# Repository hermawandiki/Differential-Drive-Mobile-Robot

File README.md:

# Differential-Drive-Mobile-Robot

This DDMR is equipped with a GUI that is able to display sensor data from the robot, control the movement of the robot, and set PID parameters for the speed of each motor.

This project was developed in the mechatronics system programming course at Mechatronics Engineering - EEPIS

Course lecturer : Adytia Darmawan, S.ST., M.T.

Mechatronics Engineering Study Program

Electronic Engineering Polytechnic Institute of Surabaya (EEPIS)

#

DDMR ini dilengkapi dengan GUI yang mampu menampilkan data sensor dari robot, mengendalikan pergerakan robot, dan mengatur parameter PID untuk kecepatan setiap motor.

Proyek ini dikembangkan dalam mata kuliah pemrograman sistem mekatronika di Teknik Mekatronika - PENS

Dosen Mata Kuliah : Adytia Darmawan, S.ST., M.T.

Program Studi Teknik Mekatronika

Politeknik Elektronika Negeri Surabaya (PENS)

#

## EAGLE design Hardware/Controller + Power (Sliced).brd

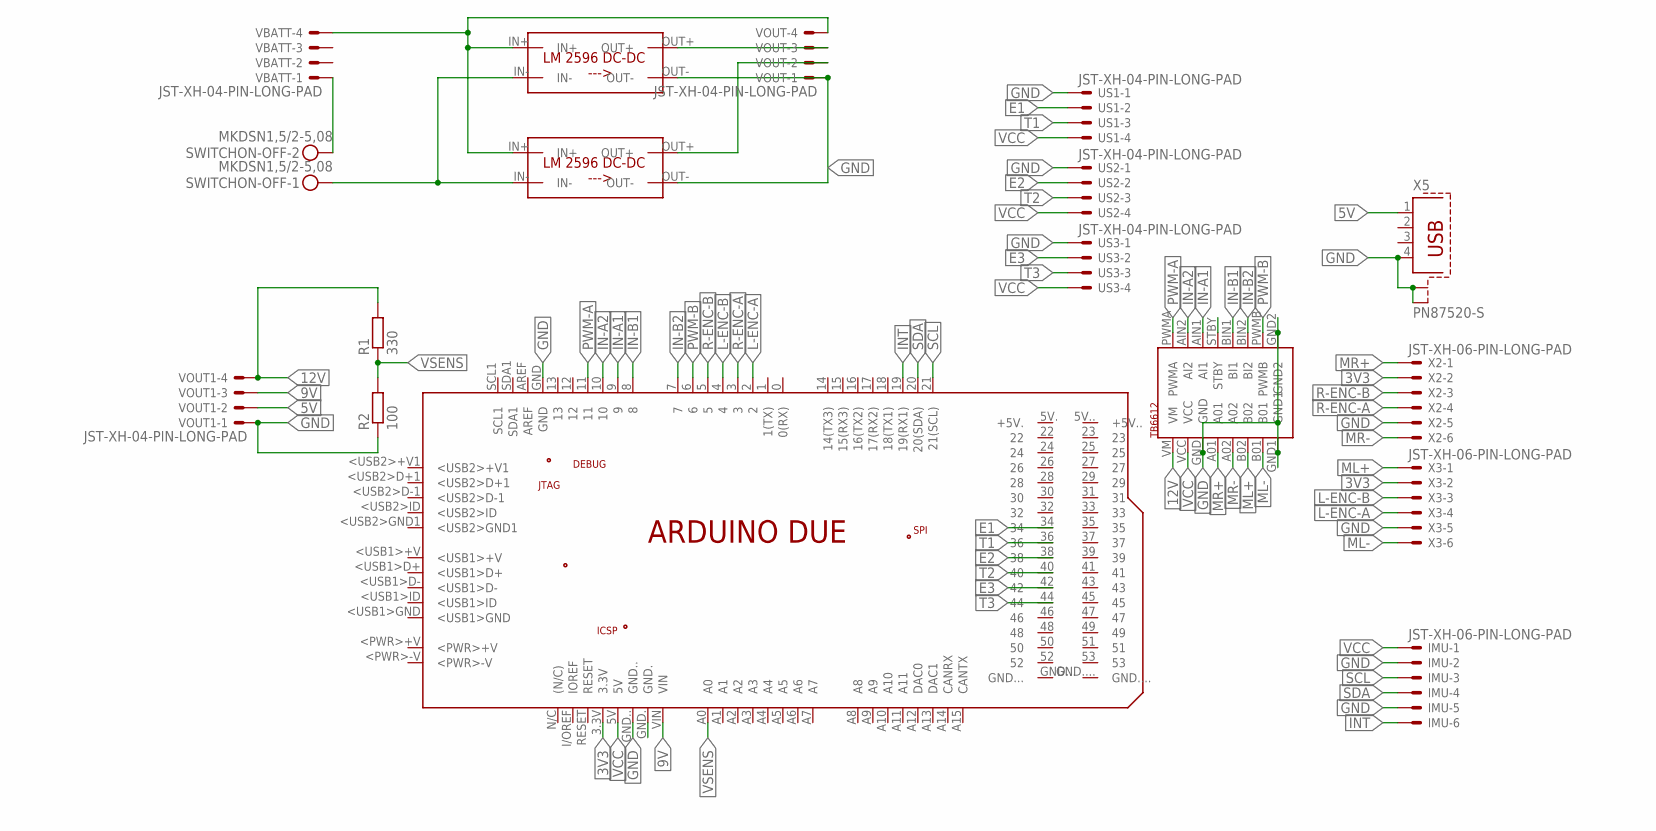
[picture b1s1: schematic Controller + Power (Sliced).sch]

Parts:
IMU: JST-XH-06-PIN-LONG-PAD; JST-XH-06-PACKAGE-LONG-PAD
PCB1: ARDUINO_DUE
R1: 330; R1206
R2: 100; R1206
SWITCHON-OFF: MKDSN1,5/2-5,08
U$1, U$2: LM2596_MODBUCK; LM2596_MOD
U$3: TB6612
US1, US2, US3: JST-XH-04-PIN-LONG-PAD; JST-XH-04-PACKAGE-LONG-PAD
VBATT: JST-XH-04-PIN-LONG-PAD; JST-XH-04-PACKAGE-LONG-PAD
VOUT, VOUT1: JST-XH-04-PIN-LONG-PAD; JST-XH-04-PACKAGE-LONG-PAD
X2, X3: JST-XH-06-PIN-LONG-PAD; JST-XH-06-PACKAGE-LONG-PAD
X5: PN87520-S

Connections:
3V3: PCB1.3.3V, X2.2, X3.2
5V: VOUT1.2, X5.1
9V: PCB1.VIN, VOUT1.3
12V: R1.2, U$3.VM, VOUT1.4
E1: PCB1.34, US1.2
E2: PCB1.38, US2.2
E3: PCB1.42, US3.2
GND: IMU.2, IMU.5, PCB1.GND, PCB1.GND.., R2.1, U$1.OUT-, U$2.OUT-, U$3.GND, U$3.GND1, U$3.GND2, US1.1, US2.1, US3.1, VOUT.1, VOUT1.1, X2.5, X3.5, X5.4, X5.S1, X5.S2
IN-A1: PCB1.9, U$3.AIN1 (AI1)
IN-A2: PCB1.10, U$3.AIN2 (AI2)
IN-B1: PCB1.8, U$3.BIN1 (BI1)
IN-B2: PCB1.7, U$3.BIN2 (BI2)
INT: IMU.6, PCB1.19 (19(RX1))
L-ENC-A: PCB1.2, X3.4
L-ENC-B: PCB1.4, X3.3
ML+: U$3.B02, X3.1
ML-: U$3.B01, X3.6
MR+: U$3.A01, X2.1
MR-: U$3.A02, X2.6
unnamed: U$1.IN+, U$2.IN+, VBATT.4, VOUT.4
unnamed: SWITCHON-OFF.2, VBATT.1
unnamed: SWITCHON-OFF.1, U$1.IN-, U$2.IN-
unnamed: U$2.OUT+, VOUT.3
unnamed: U$1.OUT+, VOUT.2
PWM-A: PCB1.11, U$3.PWMA
PWM-B: PCB1.6, U$3.PWMB
R-ENC-A: PCB1.3, X2.4
R-ENC-B: PCB1.5, X2.3
SCL: IMU.3, PCB1.21 (21(SCL))
SDA: IMU.4, PCB1.20 (20(SDA))
T1: PCB1.36, US1.3
T2: PCB1.40, US2.3
T3: PCB1.44, US3.3
VCC: IMU.1, PCB1.5V, U$3.VCC, US1.4, US2.4, US3.4
VSENS: PCB1.A0, R1.1, R2.2

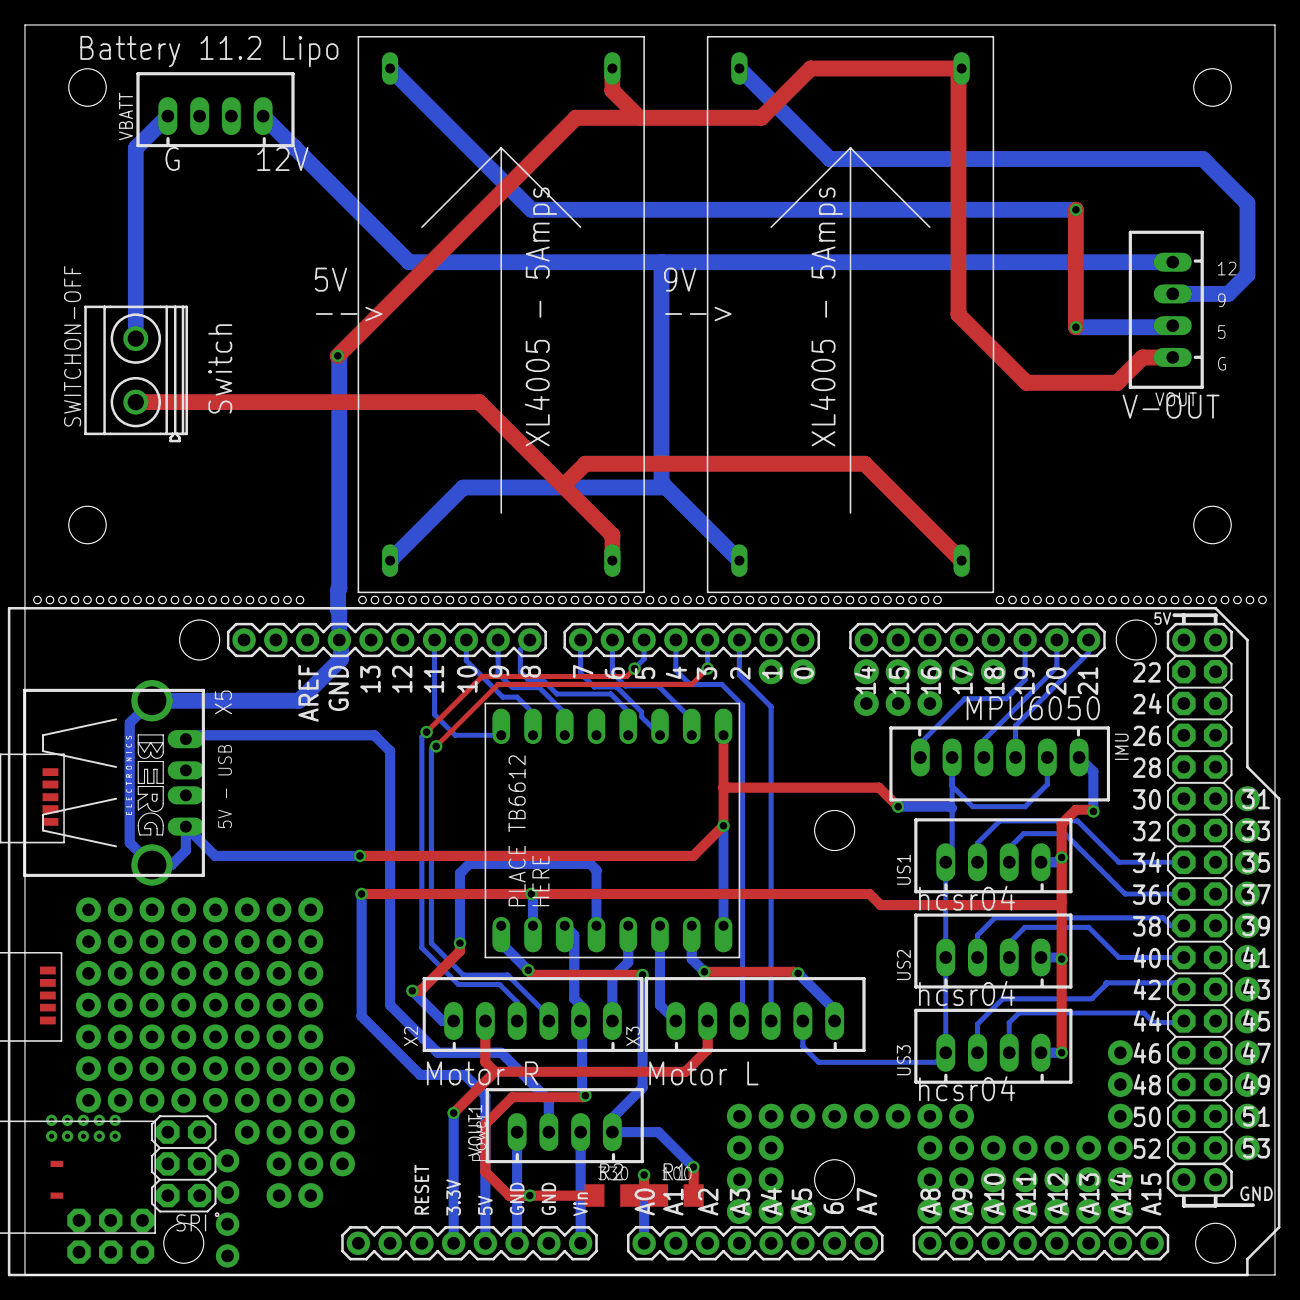
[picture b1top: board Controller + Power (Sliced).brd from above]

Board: 2 copper layers, 100.0 x 100.0 mm, 17 parts (0 on the bottom side), 35 nets.

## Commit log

2024-10-24 move from local to github
2024-10-24 from raspi, update gui
2024-10-25 update teleoperation ok
2024-10-25 update ok
2024-10-28 update, belum dicoba
2024-11-17 update insyaallah ok
2024-11-25 update final
2024-12-04 update, sudah di-review
